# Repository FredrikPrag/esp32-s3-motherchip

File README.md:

# ESP32-S3 Motherchip

A platform for testing esp32 and components with it. To later be able to make optimized products.

## esp32-hat

| Board                                       | Description               | Status                  |
|---------------------------------------------|---------------------------|-------------------------|
| [esp32-hat](esp32-hat/)                     | ESP32-S3 main board | Rev A ordered, untested |
| [micro-sd-reader-hat](micro-sd-reader-hat/) | microSD card reader | Rev A ordered, untested |

| Main board - top                                        | Bottom                                                       |
|--------------------------------------------------------|--------------------------------------------------------------|
|   |   |

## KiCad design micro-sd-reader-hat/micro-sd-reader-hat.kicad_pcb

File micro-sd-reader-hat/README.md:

## micro-sd-reader-hat

| Top                                                                        | Bottom                                                                           |
|----------------------------------------------------------------------------|----------------------------------------------------------------------------------|
|  |  |

[Schematic (PDF)](exports/micro-sd-reader-hat-schematic.pdf)

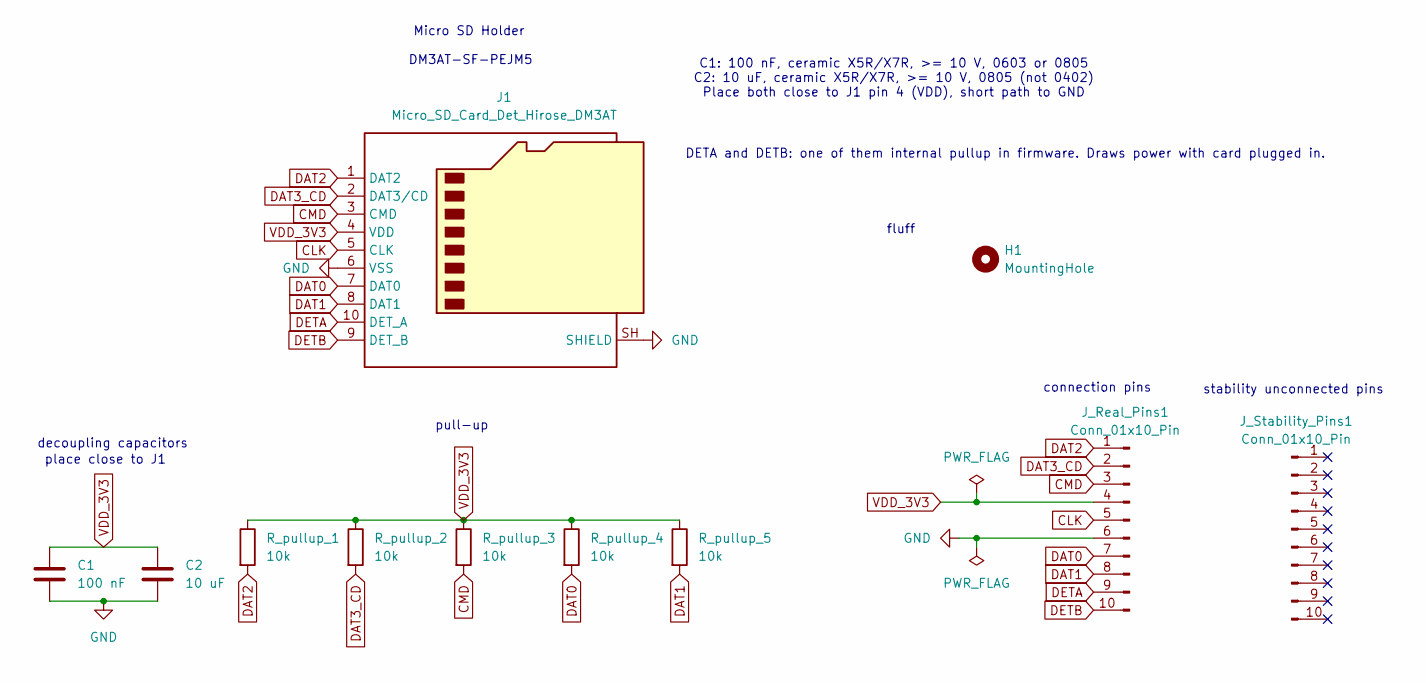
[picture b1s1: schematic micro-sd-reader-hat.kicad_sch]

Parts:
C1: 100 nF; C_0603_1608Metric_Pad1.08x0.95mm_HandSolder; Voltage 10 V
C2: 10 uF; C_0805_2012Metric_Pad1.18x1.45mm_HandSolder; Voltage 10 V
H1: MountingHole; MountingHole_2.5mm
J1: Micro_SD_Card_Det_Hirose_DM3AT; microSD_HC_Hirose_DM3AT-SF-PEJM5
J_Real_Pins1: Conn_01x10_Pin; PinHeader_1x10_P2.54mm_Vertical
J_Stability_Pins1: Conn_01x10_Pin; PinHeader_1x10_P2.54mm_Vertical
R_pullup_1, R_pullup_2, R_pullup_3, R_pullup_4, R_pullup_5: 10k; R_0805_2012Metric_Pad1.20x1.40mm_HandSolder

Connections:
CLK: J1.5 (CLK), J_Real_Pins1.5
CMD: J1.3 (CMD), J_Real_Pins1.3, R_pullup_3.2
DAT0: J1.7 (DAT0), J_Real_Pins1.7, R_pullup_4.2
DAT1: J1.8 (DAT1), J_Real_Pins1.8, R_pullup_5.2
DAT2: J1.1 (DAT2), J_Real_Pins1.1, R_pullup_1.2
DAT3_CD: J1.2 (DAT3/CD), J_Real_Pins1.2, R_pullup_2.2
DETA: J1.10 (DET_A), J_Real_Pins1.9
DETB: J1.9 (DET_B), J_Real_Pins1.10
GND: C1.2, C2.2, J1.6 (VSS), J1.SH (SHIELD), J_Real_Pins1.6
VDD_3V3: C1.1, C2.1, J1.4 (VDD), J_Real_Pins1.4, R_pullup_1.1, R_pullup_2.1, R_pullup_3.1, R_pullup_4.1, R_pullup_5.1

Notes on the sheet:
pull-up
place close to J1
connection pins
DETA and DETB: one of them internal pullup in firmware. Draws power with card plugged in.
decoupling capacitors
Micro SD Holder
C1: 100 nF, ceramic X5R/X7R, >= 10 V, 0603 or 0805 C2: 10 uF, ceramic X5R/X7R, >= 10 V, 0805 (not 0402) Place both close to J1 pin 4 (VDD), short path to GND
fluff
DM3AT-SF-PEJM5
stability unconnected pins

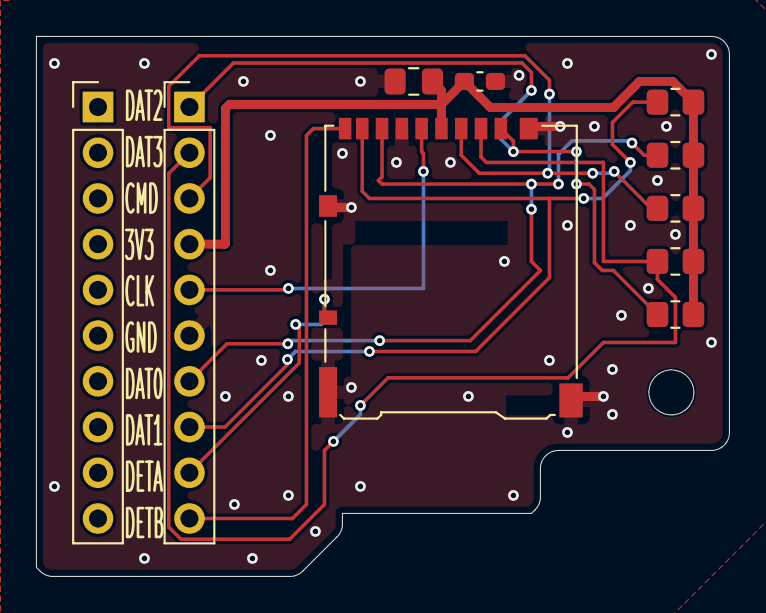
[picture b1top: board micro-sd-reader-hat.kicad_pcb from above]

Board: 2 copper layers, 38.5 x 30.0 mm, 11 parts (0 on the bottom side), 10 nets.

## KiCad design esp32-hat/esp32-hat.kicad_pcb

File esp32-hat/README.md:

## Motherchip

| Main board - top                                        | Bottom                                                       |
|--------------------------------------------------------|--------------------------------------------------------------|
|   |   |

[Schematic (PDF)](exports/esp32-hat-schematic.pdf)

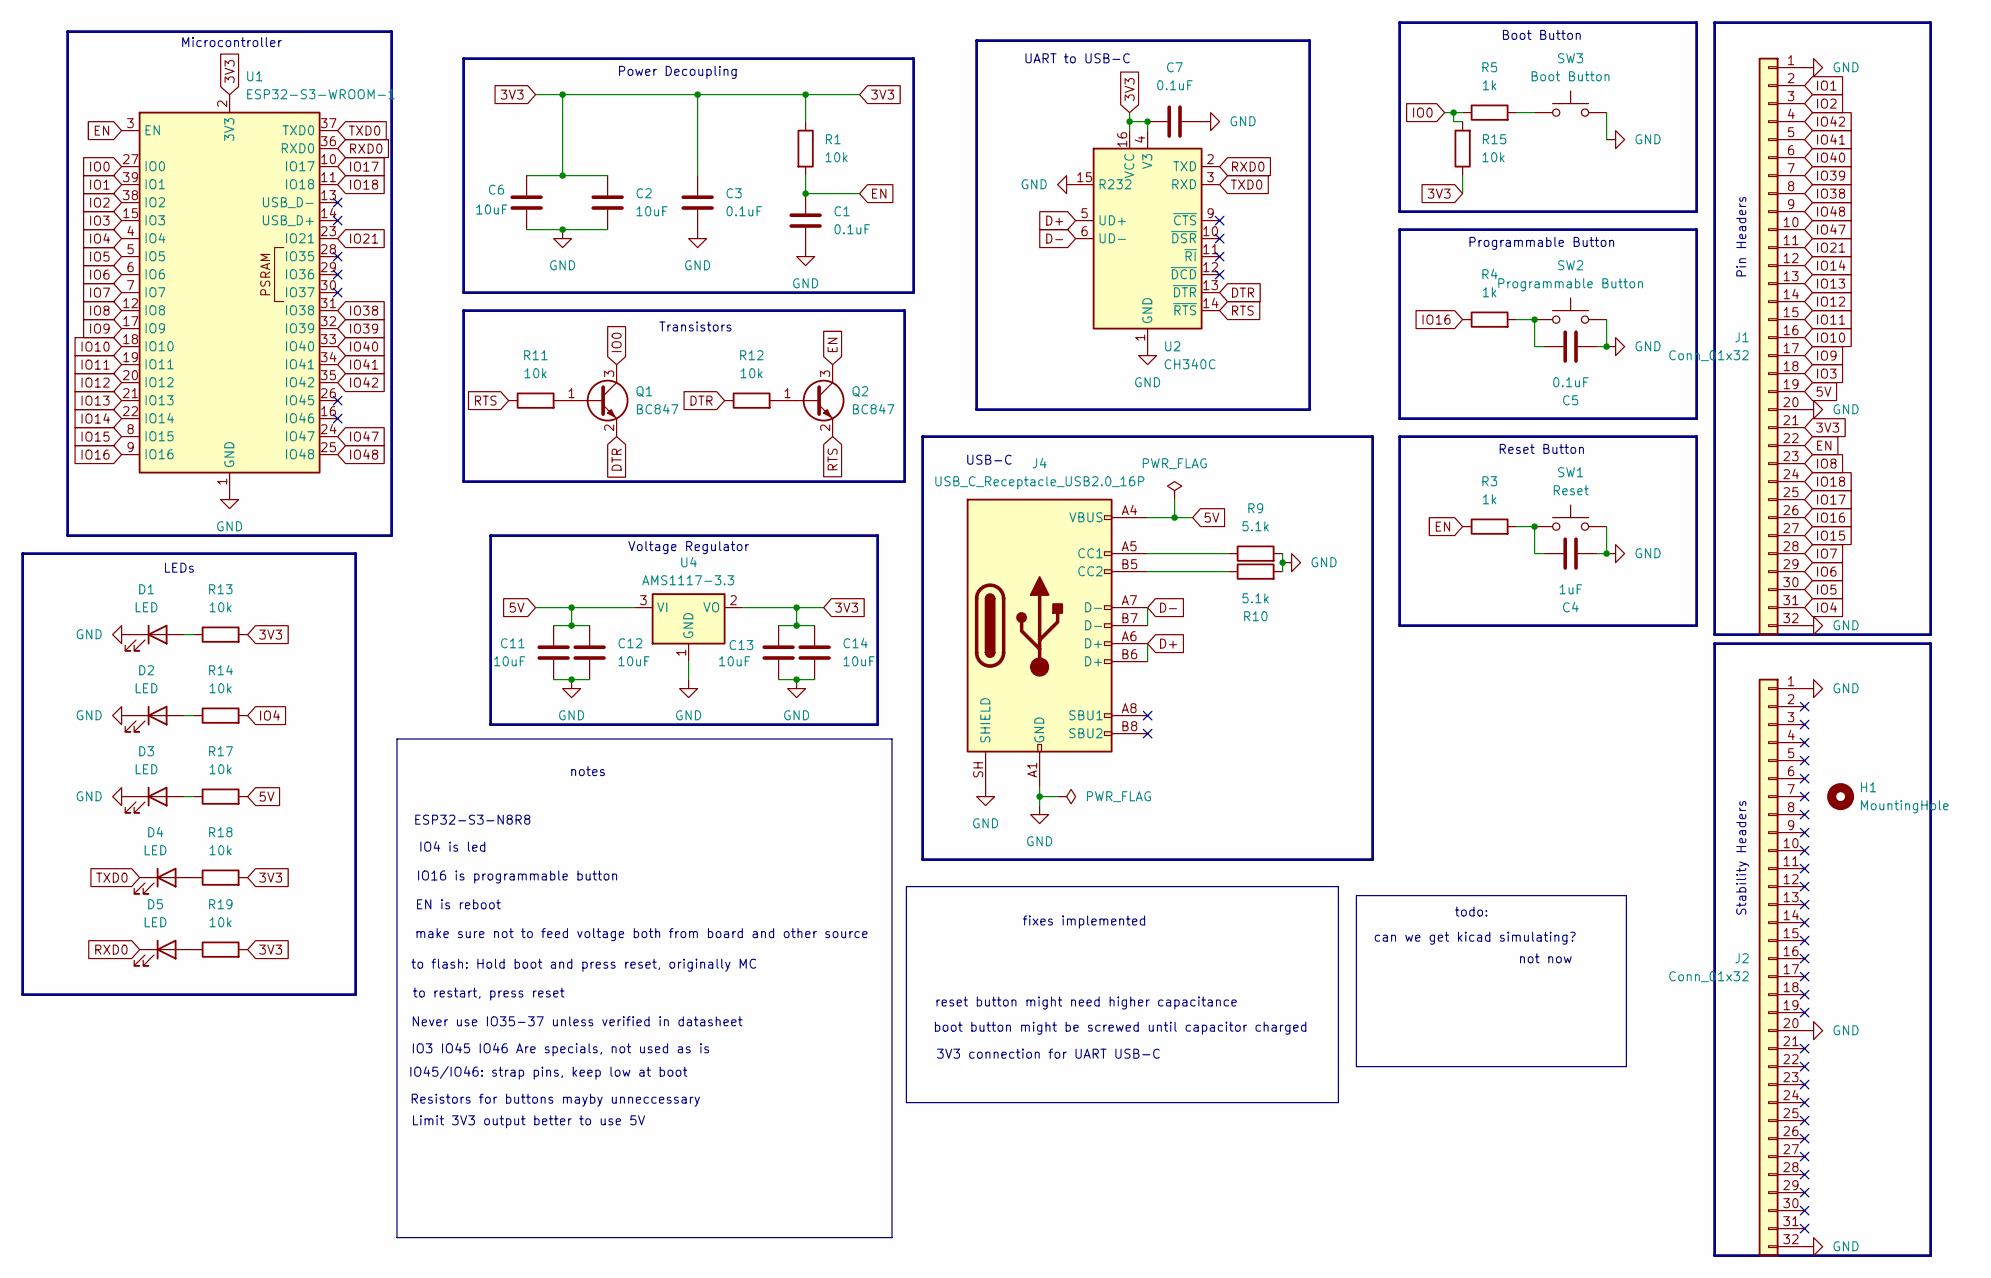
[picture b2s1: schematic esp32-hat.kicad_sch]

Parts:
C1, C3, C5, C7: 0.1uF; C_0603_1608Metric_Pad1.08x0.95mm_HandSolder
C2, C6, C11, C12, C13, C14: 10uF; C_0805_2012Metric_Pad1.18x1.45mm_HandSolder
C4: 1uF; C_0805_2012Metric_Pad1.18x1.45mm_HandSolder
D1, D2, D3, D4, D5: LED; LED_0603_1608Metric_Pad1.05x0.95mm_HandSolder
H1: MountingHole; MountingHole_2.5mm
J1, J2: Conn_01x32; PinHeader_1x32_P2.54mm_Vertical
J4: USB_C_Receptacle_USB2.0_16P; USB_C_Receptacle_HCTL_HC-TYPE-C-16P-01A
Q1, Q2: BC847; SOT-23
R1, R11, R12, R13, R14, R15, R17, R18, R19: 10k; R_0805_2012Metric_Pad1.20x1.40mm_HandSolder
R3, R4, R5: 1k; R_0805_2012Metric_Pad1.20x1.40mm_HandSolder
R9, R10: 5.1k; R_0805_2012Metric_Pad1.20x1.40mm_HandSolder
SW1: Reset; SW_SPST_TS-1088-xR020
SW2: Programmable Button; SW_SPST_TS-1088-xR020
SW3: Boot Button; SW_SPST_TS-1088-xR020
U1: ESP32-S3-WROOM-1
U2: CH340C; SOIC-16_3.9x9.9mm_P1.27mm
U4: AMS1117-3.3; SOT-223-3_TabPin2

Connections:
3V3: C2.1, C3.1, C6.1, C7.1, C13.1, C14.1, J1.21, R1.1, R13.2, R15.1, R18.2, R19.2, U1.2 (3V3), U2.4 (V3), U2.16 (VCC), U4.2 (VO)
5V: C11.1, C12.1, J1.19, J4.A4 (VBUS), J4.A9 (VBUS), J4.B4 (VBUS), J4.B9 (VBUS), R17.2, U4.3 (VI)
D+: J4.A6 (D+), J4.B6 (D+), U2.5 (UD+)
D-: J4.A7 (D-), J4.B7 (D-), U2.6 (UD-)
DTR: Q1.2 (E), R12.1, U2.13 (~DTR)
EN: C1.2, J1.22, Q2.3 (C), R1.2, R3.1, U1.3 (EN)
GND: C1.1, C2.2, C3.2, C4.1, C5.2, C6.2, C7.2, C11.2, C12.2, C13.2, C14.2, D1.1 (K), D2.1 (K), D3.1 (K), J1.1, J1.20, J1.32, J2.1, J2.20, J2.32, J4.A1 (GND), J4.A12 (GND), J4.B1 (GND), J4.B12 (GND), J4.SH (SHIELD), R9.2, R10.2, SW1.2, SW2.2, SW3.2, U1.1 (GND), U1.40 (GND), U1.41 (GND), U2.1 (GND), U2.15 (R232), U4.1 (GND)
IO0: Q1.3 (C), R5.1, R15.2, U1.27 (IO0)
IO1: J1.2, U1.39 (IO1)
IO2: J1.3, U1.38 (IO2)
IO3: J1.18, U1.15 (IO3)
IO4: J1.31, R14.2, U1.4 (IO4)
IO5: J1.30, U1.5 (IO5)
IO6: J1.29, U1.6 (IO6)
IO7: J1.28, U1.7 (IO7)
IO8: J1.23, U1.12 (IO8)
IO9: J1.17, U1.17 (IO9)
IO10: J1.16, U1.18 (IO10)
IO11: J1.15, U1.19 (IO11)
IO12: J1.14, U1.20 (IO12)
IO13: J1.13, U1.21 (IO13)
IO14: J1.12, U1.22 (IO14)
IO15: J1.27, U1.8 (IO15)
IO16: J1.26, R4.1, U1.9 (IO16)
IO17: J1.25, U1.10 (IO17)
IO18: J1.24, U1.11 (IO18)
IO21: J1.11, U1.23 (IO21)
IO38: J1.8, U1.31 (IO38)
IO39: J1.7, U1.32 (IO39)
IO40: J1.6, U1.33 (IO40)
IO41: J1.5, U1.34 (IO41)
IO42: J1.4, U1.35 (IO42)
IO47: J1.10, U1.24 (IO47)
IO48: J1.9, U1.25 (IO48)
unnamed: C4.2, R3.2, SW1.1
unnamed: C5.1, R4.2, SW2.1
unnamed: D1.2 (A), R13.1
unnamed: D2.2 (A), R14.1
unnamed: D3.2 (A), R17.1
unnamed: D4.2 (A), R18.1
unnamed: D5.2 (A), R19.1
unnamed: J4.A5 (CC1), R9.1
unnamed: J4.B5 (CC2), R10.1
unnamed: Q1.1 (B), R11.2
unnamed: Q2.1 (B), R12.2
unnamed: R5.2, SW3.1
RTS: Q2.2 (E), R11.1, U2.14 (~RTS)
RXD0: D5.1 (K), U1.36 (RXD0), U2.2 (TXD)
TXD0: D4.1 (K), U1.37 (TXD0), U2.3 (RXD)

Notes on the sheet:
Stability Headers
Resistors for buttons mayby unneccessary
ESP32-S3-N8R8
Never use IO35-37 unless verified in datasheet
LEDs
Programmable Button
Transistors
Boot Button
UART to USB-C
fixes implemented
can we get kicad simulating?
make sure not to feed voltage both from board and other source
EN is reboot
IO16 is programmable button
Voltage Regulator
Power Decoupling
not now
USB-C
notes
boot button might be screwed until capacitor charged
to flash: Hold boot and press reset, originally MC
Limit 3V3 output better to use 5V
IO3 IO45 IO46 Are specials, not used as is
reset button might need higher capacitance
Microcontroller
Reset Button
IO45/IO46: strap pins, keep low at boot
to restart, press reset
Pin Headers
IO4 is led
3V3 connection for UART USB-C
todo:

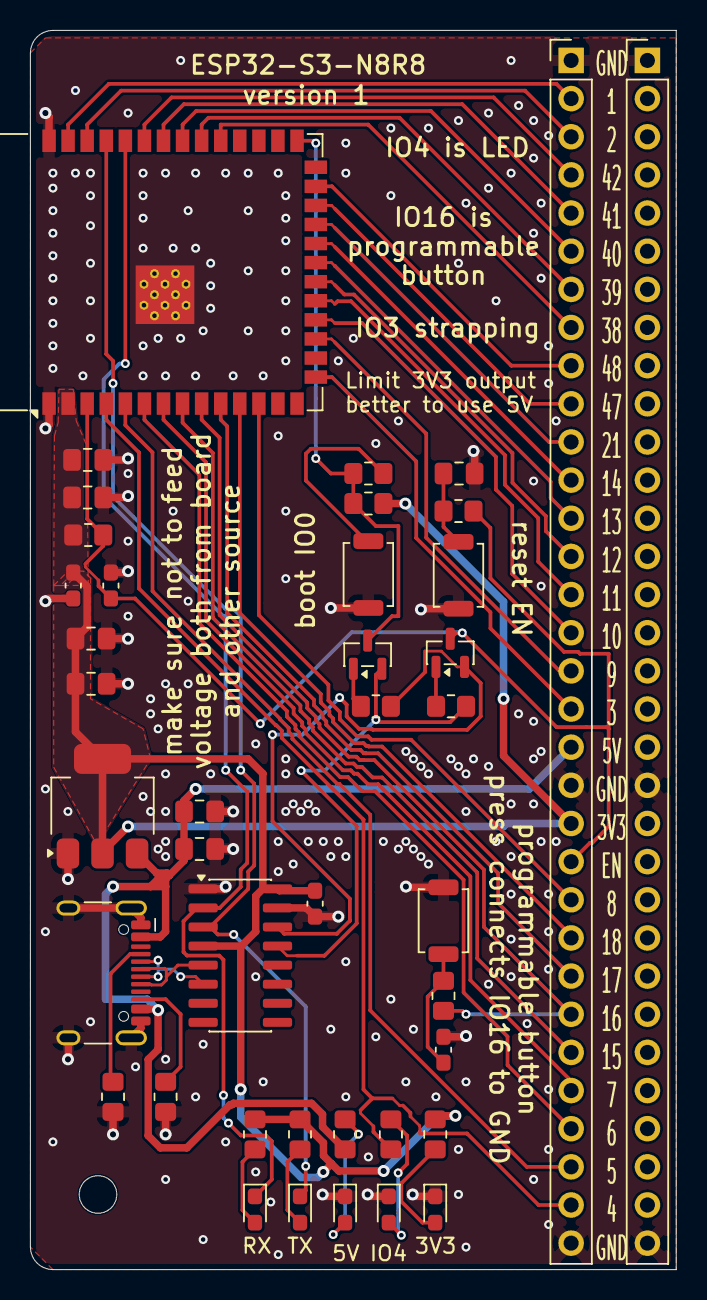
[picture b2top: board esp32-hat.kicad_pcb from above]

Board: 2 copper layers, 43.0 x 82.5 mm, 42 parts (0 on the bottom side), 49 nets.
